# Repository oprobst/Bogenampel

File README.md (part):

# Bogenampel

Eine funkgesteuerte Timer-Anzeige für Bogenschießplätze — zwei Geräte, zwei Taster,
kein Pairing, kein Netzwerk.

---

**Inhalt** — [1. Das Projekt](#1-das-projekt) · [2. Entwicklung](#2-entwicklung)

---

# 1. Das Projekt

## Optimierungspotentiale

* Auch mit dem 12-V-Buzzer ist das Signal in einer großen Halle mit Hintergrundgeräuschen noch zu leise.
Für die nächste Version wird deshalb vorgeschlagen, alternativ eine Box per Bluetooth anzuschließen.

* Weiterhin ist das Gehäuse alles andere als wartungsfreundlich. Hier sollten vor allem die Bohrungen noch mal überdacht werden.

## Worum es geht

Auf dem Schießplatz gibt eine Ampel den Takt vor: Rot heißt warten, Grün heißt
schießen, die Restzeit läuft sichtbar herunter. Die Bogenampel macht genau das —
aber ohne Kabel zwischen Schießlinie und Zielbereich, und mit so wenig Bedienung
wie möglich.

An der Bedieneinheit wird einmal der Modus vorgewählt (120 oder 240 Sekunden,
1-2 oder 3-4 Schützen), danach steuern **zwei Taster** den kompletten
Turnierablauf. Die Einstellung überlebt das Ausschalten.

Die Anlage besteht aus zwei Geräten:

- **Bedieneinheit (Sender)** — liegt an der Schießlinie. Akkubetrieben, e-Paper-Display,
  zwei große Taster.
- **Anzeigeeinheit (Empfänger)** — steht am Ziel. Große dreistellige 7-Segment-Anzeige
  aus LED-Streifen, in Ampelfarben, dazu zwei Gruppenbalken.

Dazwischen läuft ESP-NOW auf Kanal 1 — kein WLAN, kein Accesspoint, kein Pairing.
Der Sender sucht den Empfänger beim Einschalten selbst und merkt sich dessen
MAC-Adresse zur Laufzeit.

**Das wichtigste Sicherheitsmerkmal ist ein Stück Nicht-Verhalten**: Der Empfänger
zählt eine gestartete Passe **autonom** zu Ende. Fällt der Funk aus oder geht der
Sender aus, läuft der Timer trotzdem korrekt ab und schaltet danach auf Rot. Die
Anzeige bleibt nie in Grün stehen, nur weil die Verbindung weg ist.

## Die Bedieneinheit

ESP32-S3-WROOM-1U mit externer Antenne am U.FL-Anschluss, 1,54″-e-Paper
(200 × 200, SSD1681), eine 14500-LiIon-Zelle mit MCP73837-Lader und ein
Soft-Power-Latch um einen TPS62742: Einschalten per Taster, Ausschalten übernimmt
die Firmware selbst, sobald sie fertig aufgeräumt hat.
Das e-Paper behält sein Bild ohne Strom — der Abschaltbildschirm bleibt deshalb nach
dem Ausschalten lesbar stehen.

Die Platine trägt den Namen „Universal ESP32 Fernbedienung V3" — sie ist bewusst
etwas allgemeiner gehalten als nötig. Links sitzen Ladeteil und USB-C, in der Mitte
das Funkmodul mit den beiden Tastern, rechts die Ansteuerung für das e-Paper.

## Die Anzeigeeinheit

Ein XIAO ESP32C3 treibt einen WS2811-Streifen mit **66 Pixeln**: 12 für den
Gruppenbalken C/D, 12 für A/B und 3 × 14 für die dreistellige Ziffernanzeige
(2 Pixel je Segment). Versorgt wird alles aus einem USB-C-Netzteil, das über einen
CH224K-Trigger auf **12 V** verhandelt wird.

Drei Potis regeln direkt am Gerät, ohne Umweg über den Funk: **Lautstärke**,
**Helligkeit** und **Lüfterdrehzahl**. Dazu ein Piezo-Transducer für die
Signaltöne und ein temperaturunkritischer, aber hörbarer Lüfter — deshalb regelbar.

## Bedienung

Der Sender hat zwei Taster. Welcher Taster einschaltet, legt der Power-Latch in der
Hardware fest — das ist die **CONFIG**-Taste.

| Taste | kurz | 3× schnell klicken | 3 s halten |
|---|---|---|---|
| **CONFIG** | Weiter / Wert ändern | — | Ausschalten |
| **OK** | Bestätigen / Passe beenden | Alarm | Ausschalten |

Einschalten: CONFIG drücken. Ausschalten: eine der beiden Tasten 3 Sekunden halten.
Die Konfiguration (Schießzeit, Schützenzahl) bleibt im NVS erhalten und steht beim
nächsten Einschalten wieder zur Verfügung.

**Alarm**: die **OK**-Taste dreimal schnell hintereinander drücken (höchstens 0,4 s
zwischen den Klicks). Das geht im Schießbetrieb und beim Pfeileholen — also überall
dort, wo Leute an der Schießlinie stehen können. Im Konfigurationsmenü und im
Startbildschirm bleibt die Folge bewusst wirkungslos. CONFIG löst grundsätzlich
keinen Alarm aus: Diese Taste blättert durch Menüs und zählt Werte hoch, dort ist
zügiges Tippen normale Bedienung. Quittiert wird ein Alarm mit einem kurzen OK.

Ausschalten und Alarm liegen absichtlich auf **verschiedenen** Bewegungen: Halten
schaltet immer aus, egal in welchem Zustand das Gerät gerade ist. Früher hing die
Bedeutung des Haltens am Betriebszustand — wer im Schießbetrieb ausschalten wollte,
löste stattdessen einen Alarm aus.

**Automatische Abschaltung**: Wird im Konfigurationsmenü oder in „Pfeile holen" 60 Minuten
lang keine Taste gedrückt, schaltet sich der Sender selbst ab und zeigt dabei
„Automatische Abschaltung". Im Schießbetrieb und bei stehendem Alarm greift das
bewusst **nicht** — dort läuft eine Passe bzw. ein Sicherheitszustand. Gedacht ist es
gegen das im Koffer vergessene Gerät; dagegen hilft keine Stromsparmaßnahme, nur
Ausschalten.

## Ablauf einer Passe

| Phase | Anzeige | Dauer |
|---|---|---|
| **Stopp** | Rot, `000` | bis zum Start |
| **Vorbereitung** | Rot, Countdown | 10 s |
| **Schießzeit** | Grün, Countdown | 120 s oder 240 s |
| **letzte 30 s** | Orange, Countdown | 30 s |
| **Ende** | Rot, `000` | — |

Der Piezo quittiert die Phasenwechsel mit kurzen Tonfolgen (3250 Hz), das Passenende
mit drei Tönen. Ein ausgelöster Alarm blinkt und piept achtmal.

### Gruppen und halbe Passe

Bei 3-4 Schützen wird zwischen den Gruppen A/B und C/D umgeschaltet; die Anzeige folgt
einem 4er-Zyklus. Zusätzlich lässt sich eine halbe Passe starten, wenn nur noch die
zweite Gruppe schießt. Den Wechsel von der ersten auf die zweite Hälfte vollzieht der
Empfänger selbst, sobald sein Countdown abgelaufen ist — auch das gehört zur
Autonomie-Regel oben.

## Schaltpläne und Platinen

Autoritativ sind die KiCad-Projekte [`Schaltung-Sender/`](Schaltung-Sender/) und
[`Schaltung-Empfaenger/`](Schaltung-Empfaenger/). Die folgenden Exporte sind für alle
gedacht, die ohne KiCad hineinsehen wollen.

**Bedieneinheit (Sender)**

**Anzeigeeinheit (Empfänger)**

---

## 3D-Druckteile
Der 3D-Druck ist noch bei weitem nicht optimal. Manche Bohrlöcher sind redundant, manche schlecht erreichbar.

Generell wurde mit schwarzem und weißem PETG gedruckt, für die Verschraubungen wurden Einschmelzgewinde genutzt. Damit der Aufbau verstärkt wird, ist oben und unten abgewinkeltes Stahlblech über die ganze Breite verschraubt.

# 2. Entwicklung

## Hardware-Überblick

| | Sender (Bedieneinheit) | Empfänger (Anzeigeeinheit) |
|---|---|---|
| **Controller** | ESP32-S3-WROOM-1U-N16R8 (16 MB Flash, 8 MB PSRAM) | Seeed XIAO ESP32C3 |
| **Anzeige** | 1.54″ e-Paper, 200×200 (SSD1681) | LED-Strip WS2811 12 V, 66 Pixel |
| **Funk** | ESP-NOW, Kanal 1 (im Chip integriert) | ESP-NOW, Kanal 1 |
| **Versorgung** | LiIon 14500 + MCP73837-Lader, USB-C | USB-C PD 12 V über CH224K (≥ 2 A) |
| **Bedienelemente** | 2 Taster (CONFIG, OK) | Debug-Taster, 3 Potis |
| **Sonstiges** | Soft-Power-Latch (TPS62742) | Piezo 12 V, geregelter Lüfter, Pegelwandler 74AHCT1G125 |
| **Firmware** | [`Sender/`](Sender/) | [`Empfaenger/`](Empfaenger/) |
| **Schaltplan** | [`Schaltung-Sender/`](Schaltung-Sender/) | [`Schaltung-Empfaenger/`](Schaltung-Empfaenger/) |

Die verbindliche Pin-Belegung steht in
[`specs/004-v3-esp32-port/contracts/hardware-pins.md`](specs/004-v3-esp32-port/contracts/hardware-pins.md)
und wird aus den KiCad-Netzlisten abgeleitet. Bei Abweichungen gilt der Schaltplan —
Änderungen gehören zuerst dorthin, dann in den Code.

Die Empfänger-Platine erzeugt aus den 12 V zwei weitere Schienen: ein TSR0.5-2433
versorgt den XIAO mit 3,3 V, ein L7805 den Pegelwandler mit 5 V. Der LED-Strip hängt
direkt am 12-V-Netz — er kann die Logikversorgung also nicht mehr in die Knie zwingen.

## Funk

ESP-NOW auf Kanal 1, ohne externes Funkmodul und ohne Pairing: Der Sender sucht den
Empfänger beim Start per Broadcast und merkt sich dessen MAC-Adresse zur Laufzeit.

Jeder Frame ist 6 Byte groß und trägt Magic-Bytes, eine Prüfsumme und eine
Sequenznummer; der Empfänger verwirft doppelte und fehlerhafte Pakete. Übertragen
werden 11 Kommandos (Start 120/240, Stopp, Init, Alarm, Ping, Gruppenwahl, halbe Passe).
Beim Start misst der Sender die Verbindungsqualität mit 10 Pings und zeigt das Ergebnis
im Splash-Screen.

> **Ein Radio, ein Kanal.** Der ESP32 kann nicht gleichzeitig ESP-NOW auf Kanal 1 und
> WLAN auf einem anderen Kanal betreiben. Deshalb läuft im Normalbetrieb **kein** WiFi —
> weder ein Accesspoint noch eine Netzwerkverbindung. Für Updates gibt es den
> Wartungsmodus (siehe unten).

Die Protokollregeln stehen in
[`espnow-protocol.md`](specs/004-v3-esp32-port/contracts/espnow-protocol.md). Zwei
davon sind beim Ändern leicht zu übersehen:

- **Regel 3**: Ein `CMD_START` wird vom Empfänger ignoriert, solange seine
  Vorbereitungsphase bereits läuft. Beim regulären Gruppenwechsel ist das Kommando
  nur ein Sync-Signal — der Empfänger hat da längst selbst umgeschaltet.
- **FR-004a**: Beim Ablauf der Zeit sendet der Sender **nie** `CMD_STOP`. Das
  Passenende gehört dem Empfänger allein.

## Bauen und Flashen

PlatformIO ist der einzige unterstützte Build-Pfad. Die `platformio.ini` liegt **zentral
im Repo-Root**, nicht in den Firmware-Ordnern — das Repo-Root ist das Arbeitsverzeichnis.
Bibliotheken kommen über `lib_deps`, es muss nichts manuell installiert werden; die
Versionen sind **gepinnt** (FastLED 3.10.3, GxEPD2 1.6.9, Adafruit GFX 1.12.6).

```bash
pio run -e sender                 # bauen
pio run -e empfaenger

pio run -t upload -e sender       # per USB flashen
pio device monitor -e sender      # 115200 Baud

pio run -e sender-release         # Feld-Build: ohne Debug-Ausgaben und CDC-Task
```

Drei Stolpersteine, die alle wie Hardwaredefekte aussehen:

**Beim Sender muss CONFIG während des gesamten Uploads gedrückt bleiben.** Der Reset von
esptool lässt sonst den Power-Latch fallen; das Gerät schaltet sich mitten im Flashen ab
und der USB-Port verschwindet. Zu beachten: `pio run -t upload` startet esptool erst nach
gut einer Minute Build- und Dependency-Scan — so lange muss der Taster gehalten werden.
Praktischer ist, das Gerät **mit gehaltenem CONFIG einzuschalten** (dann greift der
Boot-Lockout und das Halten löst keine Power-Off-Geste aus) und esptool direkt mit den
vier Images aufzurufen.

**Die Upload-Baudrate darf nicht hochgesetzt werden** (`upload_speed = 115200` in der
`platformio.ini`). Der Sender flasht über die native USB-Serial/JTAG-Peripherie, wo die
Baudrate bedeutungslos ist — esptool wechselt beim Board-Default 460800 trotzdem, der Port
re-enumeriert dabei und der Upload stirbt mitten im Stub-Flasher mit
`PermissionError(13) ... Cannot configure port`.

**Unter Windows vor jedem Upload `$env:PYTHONIOENCODING="utf-8"` setzen.** Sonst bricht
der Vorgang mit `UnicodeEncodeError` und `[upload] Error 4294967295` ab — esptool schreibt
Unicode-Fortschrittsbalken, die eine cp1252-Konsole nicht kodieren kann. Auf den Chip
wurde zu diesem Zeitpunkt noch nichts geschrieben.

### Testlauf mit verkürzten Zeiten

Für Tests gibt es eigene Environments: Vorbereitung 5 s statt 10, Schießzeit 6 s statt
120 bzw. 12 s statt 240, Orange-Phase 2 s statt 30. Eine komplette Passe läuft damit in
unter einer Minute durch.

```bash
pio run -t upload -e empfaenger-debug-ota
pio run -t upload -e sender-debug-ota
```

Eingeschaltet wird das über `-DDEBUG_SHORT_TIMES=1` aus der `platformio.ini` — **nicht**
im Quellcode, wo ein `#ifndef`-Guard mit Default 0 steht. So kann ein Build mit
6-Sekunden-Passe nicht versehentlich im Feld landen.

> **Immer beide Geräte umstellen.** Der Empfänger zählt die Passe autonom und bekommt
> per Funk nur `CMD_START_120/240`, nie die Dauer selbst. Die Zeittabelle
> (`Timing::shootingSeconds()`) steht wortgleich in beiden `Config.h` und muss es
> bleiben — sonst endet die Passe auf zwei verschiedenen Sekunden.

### OTA-Wartungsmodus

Beide Geräte lassen sich drahtlos aktualisieren, aber nur in einem eigenen Betriebsmodus —
im Normalbetrieb ist WiFi aus (siehe Kasten oben).

- **Sender**: beide Taster gleichzeitig gedrückt halten und einschalten
- **Empfänger**: mit gehaltenem Debug-Taster (D7) einschalten

Der Sender zeigt daraufhin einen Wartungs-Screen mit WLAN-Status und **seiner eigenen
IP-Adresse**; beim Empfänger signalisiert die Status-LED durch langsames Blinken, dass er
bereit ist. Die IP wird als `upload_port` in der `platformio.ini` eingetragen (eine feste
DHCP-Reservierung ist empfehlenswert, mDNS-Namen lösen über Subnetzgrenzen nicht
zuverlässig auf).

```bash
pio run -t upload -e sender-ota            # Sender, Debug-Build (serieller Monitor bleibt)
pio run -t upload -e sender-release-ota    # Sender, Feld-Build (ohne Debug-Ausgaben/CDC)
pio run -t upload -e empfaenger-ota
```

`sender-release-ota` ist der Auslieferungsweg: gleicher Wartungsmodus, aber das
Image aus `sender-release`. Danach meldet sich kein serieller Port mehr — der
Rückweg auf den Debug-Build geht weiterhin per OTA über `sender-ota`, solange der
Wartungsmodus erreichbar bleibt.

Voraussetzung ist eine `wifi_credentials.h` im Repo-Root — Vorlage:
[`wifi_credentials.h.example`](wifi_credentials.h.example). Die Datei ist bewusst nicht
eingecheckt. Fehlt sie, meldet der Wartungsmodus das auf dem Display und wartet; einen
Accesspoint-Fallback gibt es absichtlich nicht, weil ein zweites Netz auf fremdem Kanal
ESP-NOW stilllegen würde.

Zur Fehlersuche: **ArduinoOTA lauscht auf UDP 3232, nicht TCP.** Ein TCP-Portscan meldet den
Port folgerichtig als geschlossen, auch wenn der Wartungsmodus einwandfrei läuft — daraus
lässt sich also nichts über die Erreichbarkeit ableiten. espota schickt eine UDP-Einladung,
woraufhin das Gerät eine TCP-Rückverbindung zum Host aufbaut.

Der Zugang ist nicht durch ein Passwort geschützt, sondern dadurch, dass der Modus nur mit
physisch gedrückten Tastern erreichbar ist. Grund: Das ArduinoOTA-Passwort (PBKDF2) ist mit
der `espota.py` von PlatformIO nicht kompatibel, die Authentifizierung scheitert stumm.

## Anzeige-Eigenheiten

Zwei Stellen, an denen das naheliegende Verhalten bewusst nicht implementiert ist:

**Das e-Paper blitzt nur beim Start und beim Beenden.** Ein Voll-Refresh (~2,6 s,
schwarz/weiß-Invertierung) läuft nur im Splash und auf dem Abschaltbildschirm. Alles
dazwischen — Menü, Countdown, Pfeile holen, Alarm — nutzt die Partial-Waveform und
bleibt ruhig. Restschatten werden dafür in Kauf genommen und erst beim nächsten
Einschalten weggeblitzt. Die Entwicklungsgeschichte dieser Stelle steht als Kommentar
in `Sender/EpaperDisplay.cpp`; sie ist zweimal in die andere Richtung gelaufen.

**Die Poti-Drehrichtung sitzt an genau einer Stelle**: `Poti::ASCENDING` und
`Poti::level()` in `Empfaenger/Config.h`. Alle Kennlinien rechnen mit der
Reglerstellung, nie mit dem ADC-Rohwert. Wer eine Drehrichtung umdreht, ändert das
Flag — nicht die einzelnen Kennlinien.

## Stromverbrauch des Senders

Gemessen am laufenden Gerät: **0,39 W → 0,20 W**, also etwa doppelte Akkulaufzeit.
Zwei Maßnahmen, beide in der Firmware:

| Maßnahme | Ersparnis |
|---|---|
| CPU-Takt 240 → 80 MHz (`System::CPU_FREQ_NORMAL_MHZ`) | ~10 mA |
| ESP-NOW-Empfangsfenster duty-cycled statt dauerhaft offen | ~38 mA |

Der Löwenanteil war das Funkmodul: ESP-NOW hält den Empfänger per Default dauerhaft an.
Der Sender ist nach der Discovery aber ein reiner Sender — das ACK auf eigene Frames
kommt im Sendefenster zurück, also darf das Empfangsfenster zu bleiben. Während der
Discovery wird es nur um den HELLO-Broadcast herum geöffnet. Details und Voraussetzungen
stehen in [`espnow-protocol.md`](specs/004-v3-esp32-port/contracts/espnow-protocol.md),
Regel 7.

Das **e-Paper ist für den Verbrauch praktisch irrelevant** (unter 2 %) — der
Sekundencountdown im Schießbetrieb ist bewusst nicht angetastet. Nicht möglich ist das
Abschalten des PSRAM: `CONFIG_SPIRAM=1` steckt in allen vorkompilierten
arduino-esp32-Varianten und die Initialisierung hängt nicht an `-DBOARD_HAS_PSRAM`.
Weiter runter käme man nur mit abgeschaltetem Radio zwischen den Kommandos und
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
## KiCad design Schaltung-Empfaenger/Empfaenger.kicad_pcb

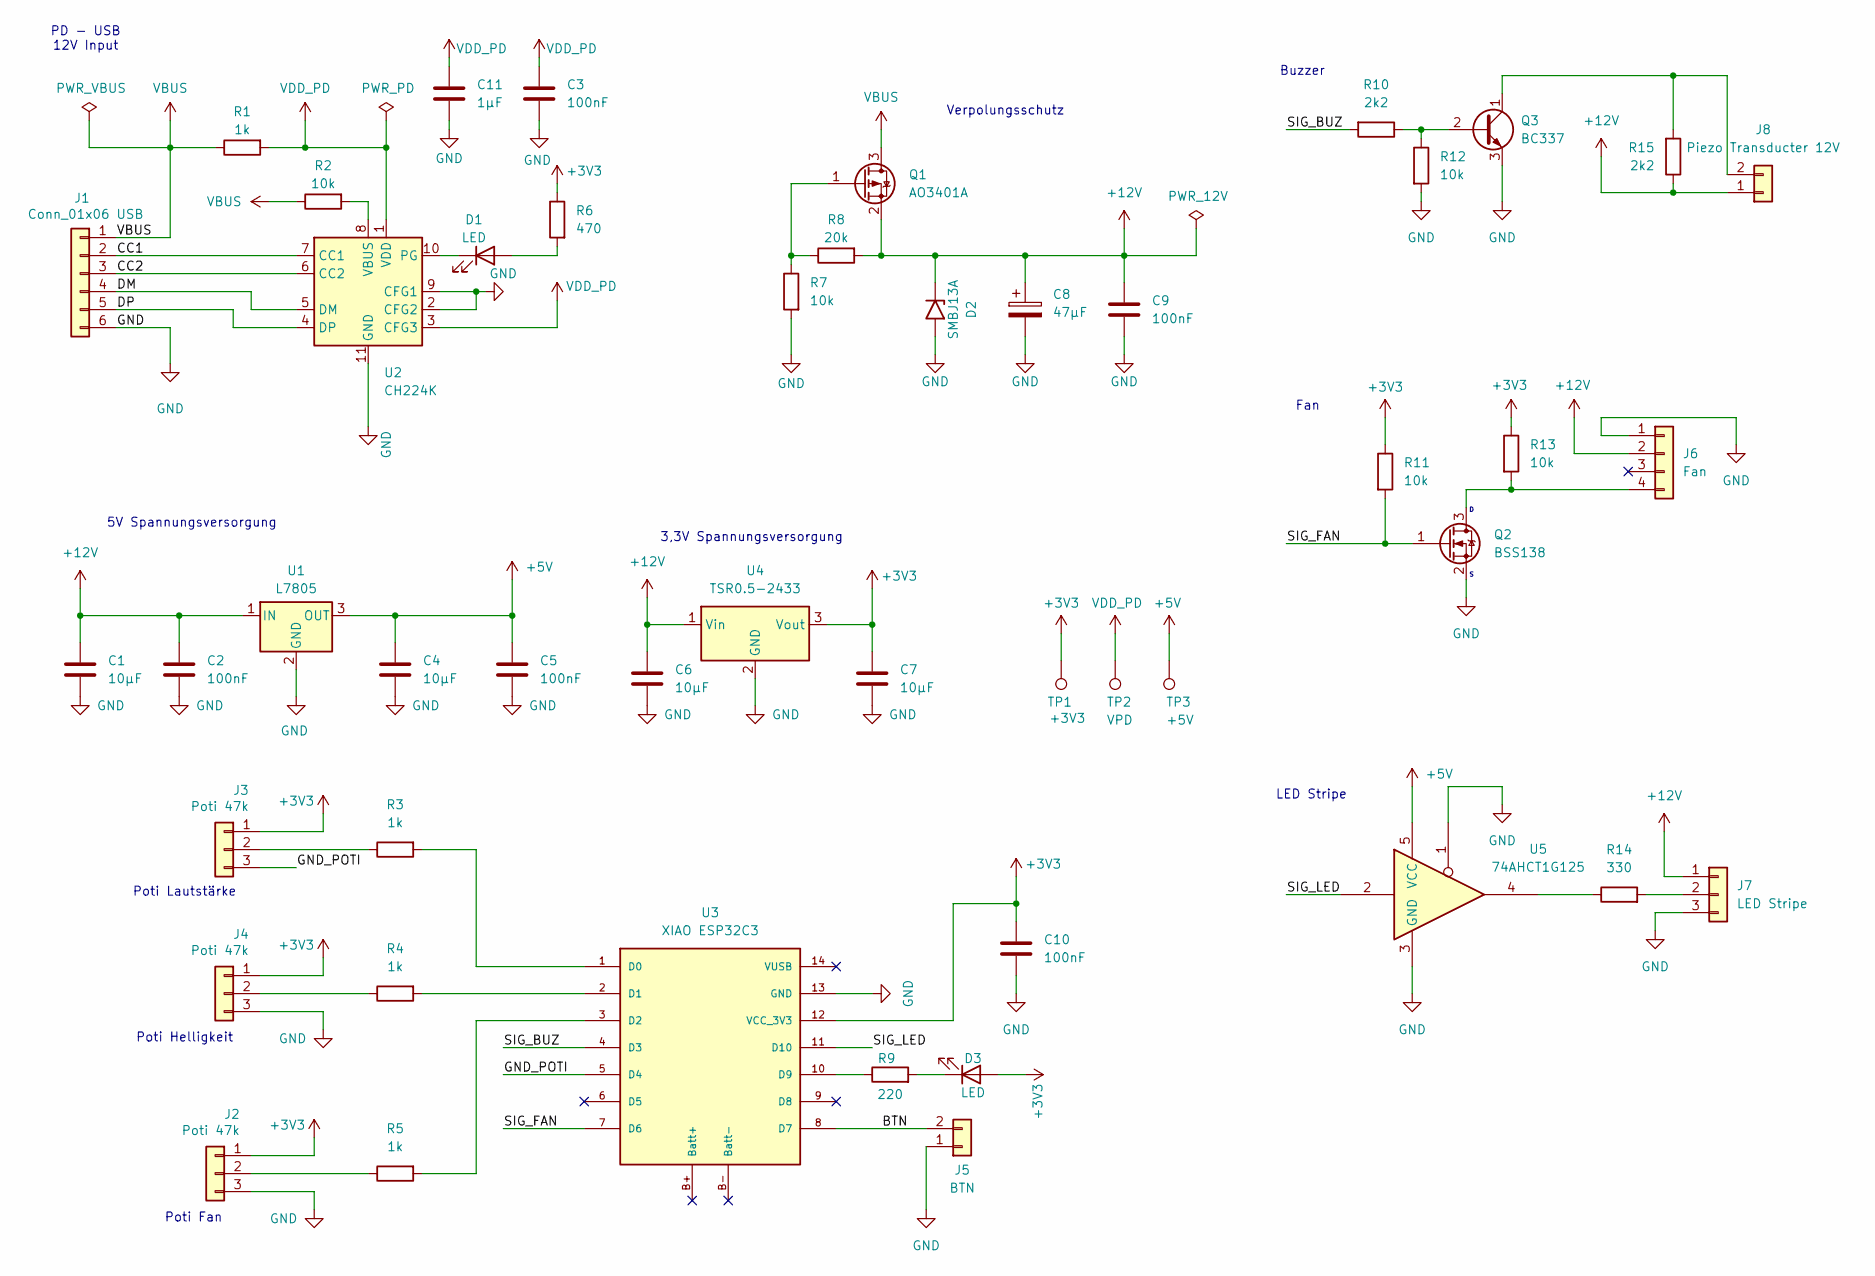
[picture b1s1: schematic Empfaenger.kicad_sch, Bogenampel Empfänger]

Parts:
C1, C4, C6, C7: 10µF; C_1206_3216Metric
C2, C3, C5, C9, C10: 100nF; C_1206_3216Metric
C8: 47µF; CP_Radial_D8.0mm_P3.50mm
C11: 1µF; C_1206_3216Metric
D1, D3: LED; LED_D5.0mm
D2: SMBJ13A; D_SMB
J1: Conn_01x06 USB; JST_XH_B6B-XH-AM_1x06_P2.50mm_Vertical
J2, J3, J4: Poti 47k; JST_XH_B3B-XH-AM_1x03_P2.50mm_Vertical
J5: BTN; JST_XH_B2B-XH-AM_1x02_P2.50mm_Vertical
J6: Fan; JST_XH_B4B-XH-AM_1x04_P2.50mm_Vertical
J7: LED Stripe; JST_XH_B3B-XH-AM_1x03_P2.50mm_Vertical
J8: Piezo Transducter 12V; JST_XH_B2B-XH-AM_1x02_P2.50mm_Vertical
Q1: AO3401A; SOT-23
Q2: BSS138; SOT-23; MPN 2N7002
Q3: BC337; TO-92_Inline
R1: 1k; R_1206_3216Metric
R2, R7, R11, R12, R13: 10k; R_0603_1608Metric
R3, R4, R5: 1k; R_0603_1608Metric
R6: 470; R_0603_1608Metric
R8: 20k; R_0603_1608Metric
R9: 220; R_0603_1608Metric
R10, R15: 2k2; R_0603_1608Metric
R14: 330; R_0603_1608Metric
TP1: +3V3; TestPoint_Pad_D1.5mm
TP2: VPD; TestPoint_Pad_D1.5mm
TP3: +5V; TestPoint_Pad_D1.5mm
U1: L7805; TO-220-3_Vertical
U2: CH224K; SSOP-10-1EP_3.9x4.9mm_P1mm_EP2.1x3.3mm
U3: XIAO ESP32C3; xiao_esp32c3
U4: TSR0.5-2433; Converter_DCDC_TRACO_TSR0.5-24xx_TSR0.5-24xxx_THT
U5: 74AHCT1G125; SOT-353_SC-70-5

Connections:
+3V3: C7.1, C10.1, D3.2 (A), J2.1, J3.1, J4.1, R6.1, R11.1, R13.1, TP1.1 (1_1), U3.12 (VCC_3V3), U4.3 (Vout)
+5V: C4.1, C5.1, TP3.1 (1_1), U1.3 (OUT), U5.5 (VCC)
+12V: C1.1, C2.1, C6.1, C8.1, C9.1, D2.1 (A1), J6.2, J7.1, J8.1, Q1.2 (S), R8.2, R15.1, U1.1 (IN), U4.1 (Vin)
/BTN: J5.2, U3.8 (D7)
/CC1: J1.2, U2.7 (CC1)
/CC2: J1.3, U2.6 (CC2)
/DM: J1.4, U2.5 (DM)
/DP: J1.5, U2.4 (DP)
/GND_POTI: J3.3, U3.5 (D4)
/SIG_BUZ: R10.2, U3.4 (D3)
/SIG_FAN: Q2.1 (G), R11.2, U3.7 (D6)
/SIG_LED: U3.11 (D10), U5.2
GND: C1.2, C2.2, C3.2, C4.2, C5.2, C6.2, C7.2, C8.2, C9.2, C10.2, C11.2, D2.2 (A2), J1.6, J2.3, J4.3, J5.1, J6.1, J7.3, Q2.2 (S), Q3.3 (E), R7.2, R12.2, U1.2 (GND), U2.2 (CFG2), U2.9 (CFG1), U2.11 (GND), U3.13 (GND), U4.2 (GND), U5.1, U5.3 (GND)
unnamed: D1.2 (A), R6.2
unnamed: D1.1 (K), U2.10 (PG)
unnamed: D3.1 (K), R9.2
unnamed: J2.2, R5.1
unnamed: J3.2, R3.1
unnamed: J4.2, R4.1
unnamed: J6.4, Q2.3 (D), R13.2
unnamed: J7.2, R14.2
unnamed: J8.2, Q3.1 (C), R15.2
unnamed: Q1.1 (G), R7.1, R8.1
unnamed: Q3.2 (B), R10.1, R12.1
unnamed: R14.1, U5.4
unnamed: R2.2, U2.8 (VBUS)
unnamed: R3.2, U3.1 (D0)
unnamed: R4.2, U3.2 (D1)
unnamed: R5.2, U3.3 (D2)
unnamed: R9.1, U3.10 (D9)
VBUS: J1.1, Q1.3 (D), R1.1, R2.1
VDD_PD: C3.1, C11.1, R1.2, TP2.1 (1_1), U2.1 (VDD), U2.3 (CFG3)

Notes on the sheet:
Poti Lautstärke
Buzzer
Poti Helligkeit
LED Stripe
Fan
Verpolungsschutz
Poti Fan
3,3V Spannungsversorgung
5V Spannungsversorgung
PD - USB 12V Input

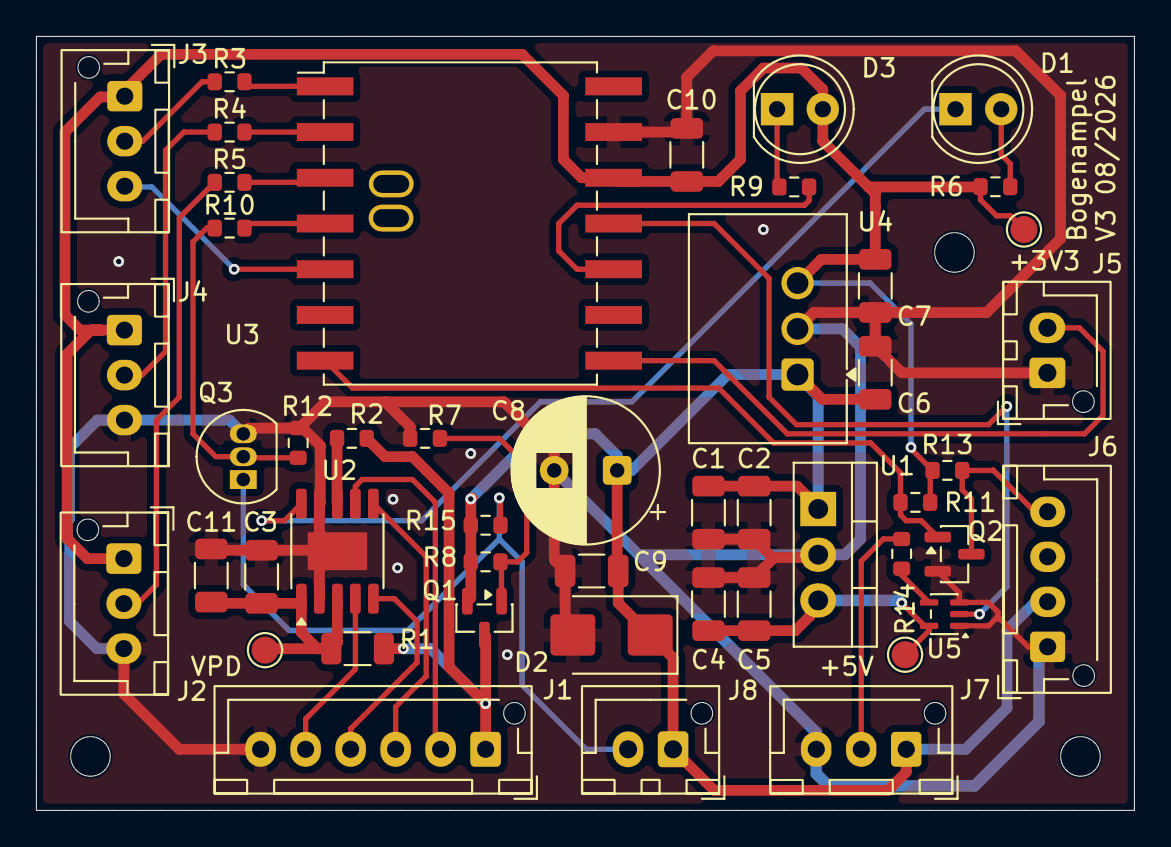
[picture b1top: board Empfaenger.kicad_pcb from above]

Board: 2 copper layers, 61.0 x 43.0 mm, 48 parts (0 on the bottom side), 32 nets.

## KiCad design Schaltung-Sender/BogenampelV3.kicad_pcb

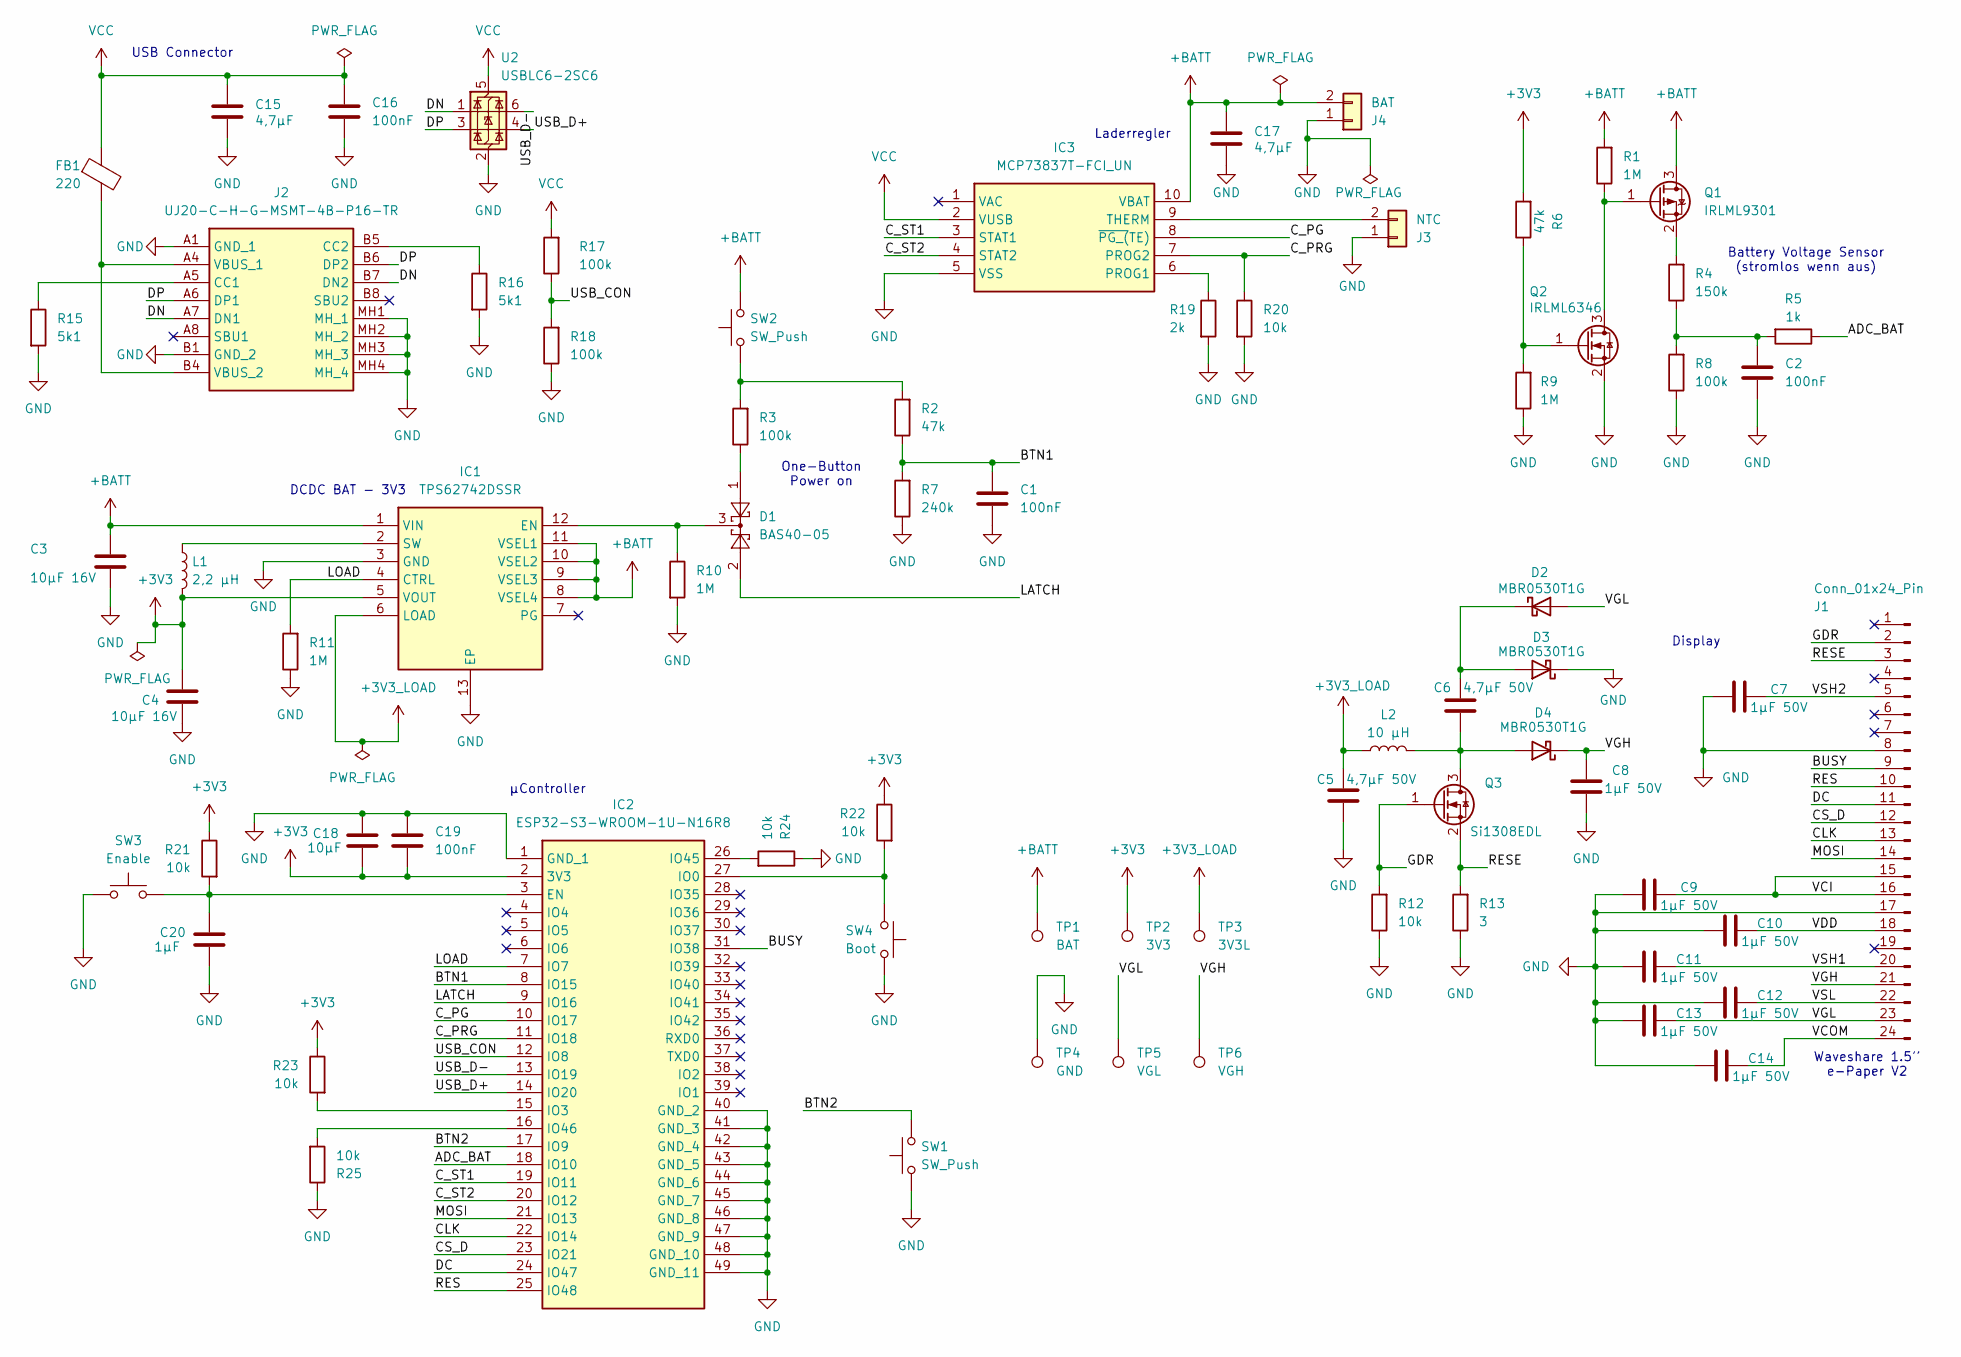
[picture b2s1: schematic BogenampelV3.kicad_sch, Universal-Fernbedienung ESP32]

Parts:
C1, C16, C19: 100nF; C_0603_1608Metric
C2: 100nF; C_0805_2012Metric
C3, C4: 10µF 16V; C_0805_2012Metric
C5, C6: 4,7µF 50V; C_1206_3216Metric
C7, C8, C9, C10, C11, C12, C13, C14: 1µF 50V; C_0805_2012Metric
C15, C17: 4,7µF; C_0805_2012Metric
C18: 10µF; C_0805_2012Metric
C20: 1µF; C_0805_2012Metric
D1: BAS40-05; SOT-23
D2, D3, D4: MBR0530T1G; D_SOD-123
FB1: 220; R_0805_2012Metric
IC1: TPS62742DSSR; SON50P200X300X80-13N-D; Mouser Part Number 595-TPS62742DSSR
IC2: ESP32-S3-WROOM-1U-N16R8; ESP32S3WROOM1UN16R8; Mouser Part Number 356-ESP32S3WM1UN16R8
IC3: MCP73837T-FCI_UN; SOP50P490X110-10N; Mouser Part Number 579-MCP73837T-FCI/UN
J1: Conn_01x24_Pin; Hirose_FH12-24S-0.5SH_1x24-1MP_P0.50mm_Horizontal
J2: UJ20-C-H-G-MSMT-4B-P16-TR; UJ20CHGMSMT4BP16TR; Manufacturer_Part_Number UJ20-C-H-G-MSMT-4B-P16-TR
J3: NTC; PinHeader_1x02_P2.54mm_Vertical; MPN 61300211121
J4: BAT; PinHeader_1x02_P2.54mm_Vertical; MPN 61300211121
L1: 2,2 µH; L_Coilcraft_LPS3314
L2: 10 µH; L_Coilcraft_LPS3314
Q1: IRLML9301; SOT-23
Q2: IRLML6346; SOT-23
Q3: Si1308EDL; SOT-323_SC-70
R1, R9, R10, R11: 1M; R_1206_3216Metric
R2, R6: 47k; R_1206_3216Metric
R3, R8, R17, R18: 100k; R_1206_3216Metric
R4: 150k; R_1206_3216Metric
R5: 1k; R_1206_3216Metric
R7: 240k; R_1206_3216Metric
R12, R20, R21, R22, R23, R24, R25: 10k; R_1206_3216Metric
R13: 3; R_1206_3216Metric
R15, R16: 5k1; R_1206_3216Metric
R19: 2k; R_1206_3216Metric
SW1, SW2: SW_Push; SW_PUSH-12mm_Wuerth-430476085716
SW3: Enable; SW_PUSH_6mm_H5mm
SW4: Boot; SW_PUSH_6mm_H5mm
TP1: BAT; TestPoint_Pad_D1.5mm
TP2: 3V3; TestPoint_Pad_D1.5mm
TP3: 3V3L; TestPoint_Pad_D1.5mm
TP4: GND; TestPoint_Pad_1.5x1.5mm
TP5: VGL; TestPoint_Pad_D1.5mm
TP6: VGH; TestPoint_Pad_D1.5mm
U2: USBLC6-2SC6; SOT-23-6

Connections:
+3V3: C4.1, C18.2, C19.2, IC1.5 (VOUT), IC2.2 (3V3), L1.2, R6.2, R21.1, R22.1, R23.1, TP2.1 (1_1)
+3V3_LOAD: C5.1, IC1.6 (LOAD), L2.1, TP3.1 (1_1)
+BATT: C3.1, C17.1, IC1.1 (VIN), IC1.8 (VSEL4), IC1.9 (VSEL3), IC1.10 (VSEL2), IC1.11 (VSEL1), IC3.10 (VBAT), J4.2, Q1.3 (D), R1.2, SW2.2, TP1.1 (1_1)
/ADC_BAT: IC2.18 (IO10), R5.1
/BTN1: C1.1, IC2.8 (IO15), R2.1, R7.2
/BTN2: IC2.17 (IO9), SW1.2
/BUSY: IC2.31 (IO38), J1.9
/CLK: IC2.22 (IO14), J1.13
/CS_D: IC2.23 (IO21), J1.12
/C_PG: IC2.10 (IO17), IC3.8 (~PG_(TE))
/C_PRG: IC2.11 (IO18), IC3.7 (PROG2), R20.1
/C_ST1: IC2.19 (IO11), IC3.3 (STAT1)
/C_ST2: IC2.20 (IO12), IC3.4 (STAT2)
/DC: IC2.24 (IO47), J1.11
/DN: J2.A7 (DN1), J2.B7 (DN2), U2.1 (I/O1)
/DP: J2.A6 (DP1), J2.B6 (DP2), U2.3 (I/O2)
/GDR: J1.2, Q3.1 (G), R12.2
/LATCH: D1.2, IC2.9 (IO16)
/LOAD: IC1.4 (CTRL), IC2.7 (IO7), R11.2
/MOSI: IC2.21 (IO13), J1.14
/RES: IC2.25 (IO48), J1.10
/RESE: J1.3, Q3.2 (S), R13.2
/USB_CON: IC2.12 (IO8), R17.1, R18.2
/USB_D+: IC2.14 (IO20), U2.4 (I/O2)
/USB_D-: IC2.13 (IO19), U2.6 (I/O1)
/VCI: C9.2, J1.15, J1.16
/VCOM: C14.2, J1.24
/VDD: C10.2, J1.18
/VGH: C8.2, D4.1 (K), J1.21, TP6.1 (1_1)
/VGL: C13.2, D2.2 (A), J1.23, TP5.1 (1_1)
/VSH1: C11.2, J1.20
/VSH2: C7.2, J1.5
/VSL: C12.2, J1.22
GND: C1.2, C2.2, C3.2, C4.2, C5.2, C7.1, C8.1, C9.1, C10.1, C11.1, C12.1, C13.1, C14.1, C15.2, C16.2, C17.2, C18.1, C19.1, C20.2, D3.1 (K), IC1.3 (GND), IC1.13 (EP), IC2.1 (GND_1), IC2.40 (GND_2), IC2.41 (GND_3), IC2.42 (GND_4), IC2.43 (GND_5), IC2.44 (GND_6), IC2.45 (GND_7), IC2.46 (GND_8), IC2.47 (GND_9), IC2.48 (GND_10), IC2.49 (GND_11), IC3.5 (VSS), J1.8, J1.17, J2.A1 (GND_1), J2.B1 (GND_2), J2.MH1 (MH_1), J2.MH2 (MH_2), J2.MH3 (MH_3), J2.MH4 (MH_4), J3.1, J4.1, Q2.2 (S), R7.1, R8.1, R9.1, R10.2, R11.1, R12.1, R13.1, R15.2, R16.2, R18.1, R19.2, R20.2, R24.1, R25.1, SW1.1, SW3.1, SW4.1, TP4.1 (1_1), U2.2 (GND)
unnamed: C2.1, R4.1, R5.2, R8.2
unnamed: D1.1, R3.1
unnamed: C6.2, D2.1 (K), D3.2 (A)
unnamed: C6.1, D4.2 (A), L2.2, Q3.3 (D)
unnamed: D1.3, IC1.12 (EN), R10.1
unnamed: IC1.2 (SW), L1.1
unnamed: C20.1, IC2.3 (EN), R21.2, SW3.2
unnamed: IC2.27 (IO0), R22.2, SW4.2
unnamed: IC2.15 (IO3), R23.2
unnamed: IC2.26 (IO45), R24.2
unnamed: IC2.16 (IO46), R25.2
unnamed: IC3.6 (PROG1), R19.1
unnamed: IC3.9 (THERM), J3.2
unnamed: J2.A5 (CC1), R15.1
unnamed: J2.B5 (CC2), R16.1
unnamed: FB1.2, J2.A4 (VBUS_1), J2.B4 (VBUS_2)
unnamed: Q1.1 (G), Q2.3 (D), R1.1
unnamed: Q1.2 (S), R4.2
unnamed: Q2.1 (G), R6.1, R9.2
unnamed: R2.2, R3.2, SW2.1
VCC: C15.1, C16.1, FB1.1, IC3.2 (VUSB), R17.2, U2.5 (VBUS)

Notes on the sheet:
USB Connector
Battery Voltage Sensor (stromlos wenn aus)
One-Button Power on
µController
Laderregler
Display
DCDC BAT - 3V3
Waveshare 1.5'' e-Paper V2

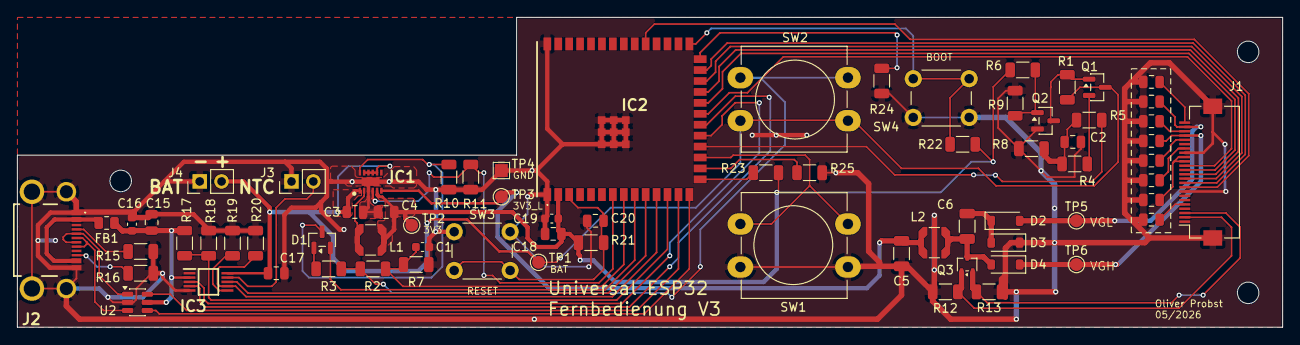
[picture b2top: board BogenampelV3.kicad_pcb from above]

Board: 2 copper layers, 147.0 x 36.0 mm, 72 parts (0 on the bottom side), 55 nets.

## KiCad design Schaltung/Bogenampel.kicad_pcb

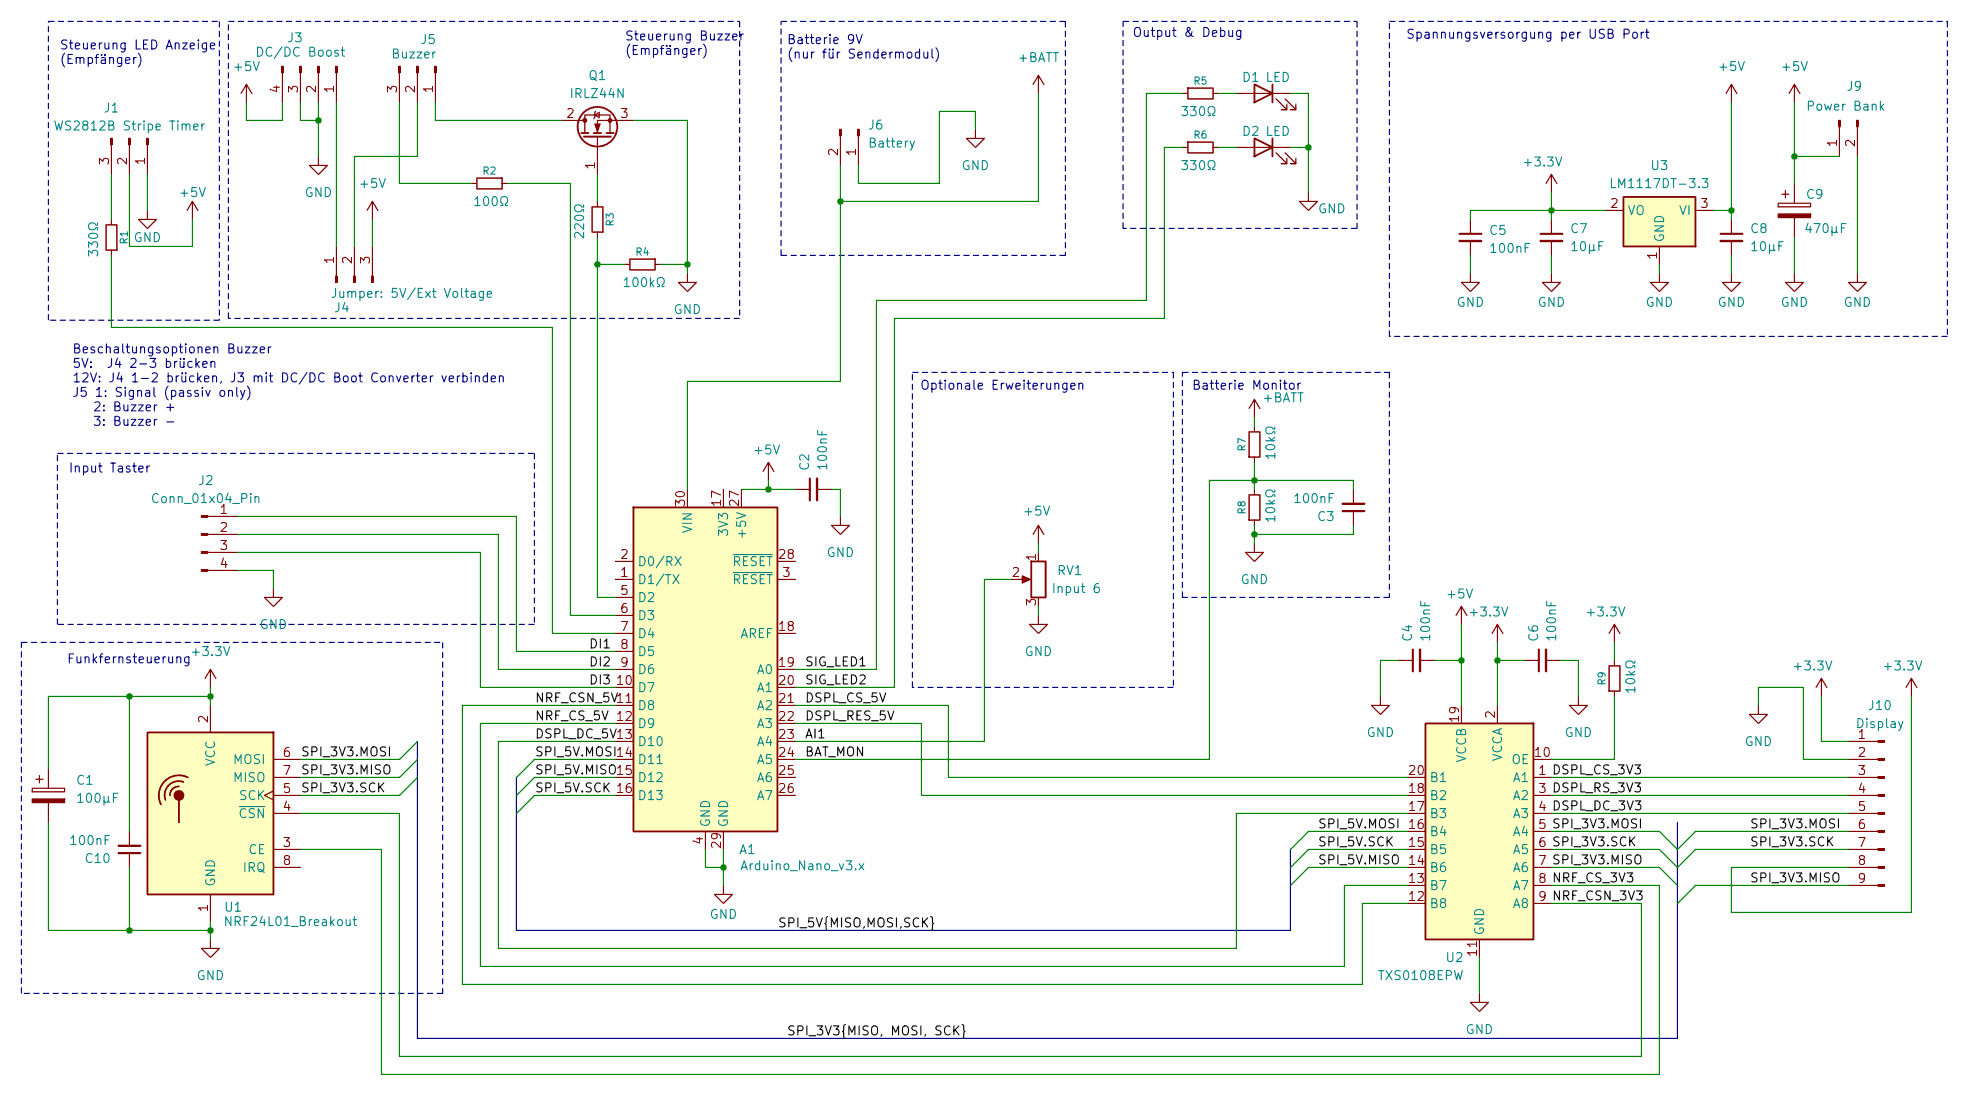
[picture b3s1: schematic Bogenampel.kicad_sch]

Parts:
A1: Arduino_Nano_v3.x; Arduino_Nano
C1: 100µF; CP_Radial_D8.0mm_P3.50mm
C2, C3, C4, C5, C6, C10: 100nF; C_1206_3216Metric
C7, C8: 10µF; C_1206_3216Metric
C9: 470µF; CP_Radial_D8.0mm_P3.50mm
D1, D2: LED; LED_D3.0mm
J1: WS2812B Stripe Timer; PhoenixContact_MCV_1,5_3-G-5.08_1x03_P5.08mm_Vertical
J2: Conn_01x04_Pin; JST_XH_B4B-XH-A_1x04_P2.50mm_Vertical
J3: DC/DC Boost; JST_XH_B4B-XH-A_1x04_P2.50mm_Vertical
J4: Jumper: 5V/Ext Voltage; PinHeader_1x03_P2.54mm_Vertical
J5: Buzzer; JST_XH_B3B-XH-A_1x03_P2.50mm_Vertical
J6: Battery; JST_XH_B2B-XH-A_1x02_P2.50mm_Vertical
J9: Power Bank; PhoenixContact_MCV_1,5_2-G-5.08_1x02_P5.08mm_Vertical
J10: Display; JST_EH_B9B-EH-A_1x09_P2.50mm_Vertical
Q1: IRLZ44N; TO-220-3_Vertical
R1, R5, R6: 330Ω; R_1206_3216Metric
R2: 100Ω; R_1206_3216Metric
R3: 220Ω; R_1206_3216Metric
R4: 100kΩ; R_1206_3216Metric
R7, R8, R9: 10kΩ; R_1206_3216Metric
RV1: Input 6; JST_XH_B3B-XH-A_1x03_P2.50mm_Vertical
U1: NRF24L01_Breakout; nRF24L01_Breakout
U2: TXS0108EPW; TSSOP-20_4.4x6.5mm_P0.65mm
U3: LM1117DT-3.3; TO-252-3_TabPin2

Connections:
+3.3V: C1.1, C5.1, C6.1, C7.1, C10.2, J10.1, J10.8, R9.2, U1.2 (VCC), U2.2 (VCCA), U3.2 (VO)
+5V: A1.27 (+5V), C2.1, C4.2, C8.1, C9.1, J1.2, J3.4, J4.3, J9.1, RV1.1, U2.19 (VCCB), U3.3 (VI)
+BATT: A1.30 (VIN), J6.2, R7.2
/AI1: A1.23 (A4), RV1.2
/BAT_MON: A1.24 (A5), C3.2, R7.1, R8.2
/DI1: A1.8 (D5), J2.1
/DI2: A1.9 (D6), J2.2
/DI3: A1.10 (D7), J2.3
/DSPL_CS_3V3: J10.3, U2.1 (A1)
/DSPL_CS_5V: A1.21 (A2), U2.20 (B1)
/DSPL_DC_3V3: J10.5, U2.4 (A3)
/DSPL_DC_5V: A1.13 (D10), U2.17 (B3)
/DSPL_RES_5V: A1.22 (A3), U2.18 (B2)
/DSPL_RS_3V3: J10.4, U2.3 (A2)
/NRF_CSN_3V3: U1.4 (~CSN), U2.9 (A8)
/NRF_CSN_5V: A1.11 (D8), U2.12 (B8)
/NRF_CS_3V3: U1.3 (CE), U2.8 (A7)
/NRF_CS_5V: A1.12 (D9), U2.13 (B7)
/SIG_LED1: A1.19 (A0), R5.1
/SIG_LED2: A1.20 (A1), R6.1
/SPI_3V3.MISO: J10.9, U1.7 (MISO), U2.7 (A6)
/SPI_3V3.MOSI: J10.6, U1.6 (MOSI), U2.5 (A4)
/SPI_3V3.SCK: J10.7, U1.5 (SCK), U2.6 (A5)
/SPI_5V.MISO: A1.15 (D12), U2.14 (B6)
/SPI_5V.MOSI: A1.14 (D11), U2.16 (B4)
/SPI_5V.SCK: A1.16 (D13), U2.15 (B5)
GND: A1.4 (GND), A1.29 (GND), C1.2, C2.2, C3.1, C4.1, C5.2, C6.2, C7.2, C8.2, C9.2, C10.1, D1.1 (K), D2.1 (K), J1.1, J2.4, J3.2, J3.3, J6.1, J9.2, J10.2, Q1.3 (S), R4.1, R8.1, RV1.3, U1.1 (GND), U2.11 (GND), U3.1 (GND)
unnamed: A1.5 (D2), R3.1, R4.2
unnamed: A1.6 (D3), R2.1
unnamed: A1.7 (D4), R1.1
unnamed: D1.2 (A), R5.2
unnamed: D2.2 (A), R6.2
unnamed: J1.3, R1.2
unnamed: J3.1, J4.1
unnamed: J4.2, J5.2
unnamed: J5.1, Q1.2 (D)
unnamed: J5.3, R2.2
unnamed: Q1.1 (G), R3.2
unnamed: R9.1, U2.10 (OE)

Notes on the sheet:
Steuerung Buzzer (Empfänger)
Beschaltungsoptionen Buzzer 5V: J4 2-3 brücken 12V: J4 1-2 brücken, J3 mit DC/DC Boot Converter verbinden J5 1: Signal (passiv only) 2: Buzzer + 3: Buzzer -
Input Taster
Steuerung LED Anzeige (Empfänger)
Spannungsversorgung per USB Port
Batterie 9V (nur für Sendermodul)
Batterie Monitor
Optionale Erweiterungen
Funkfernsteuerung
Output & Debug

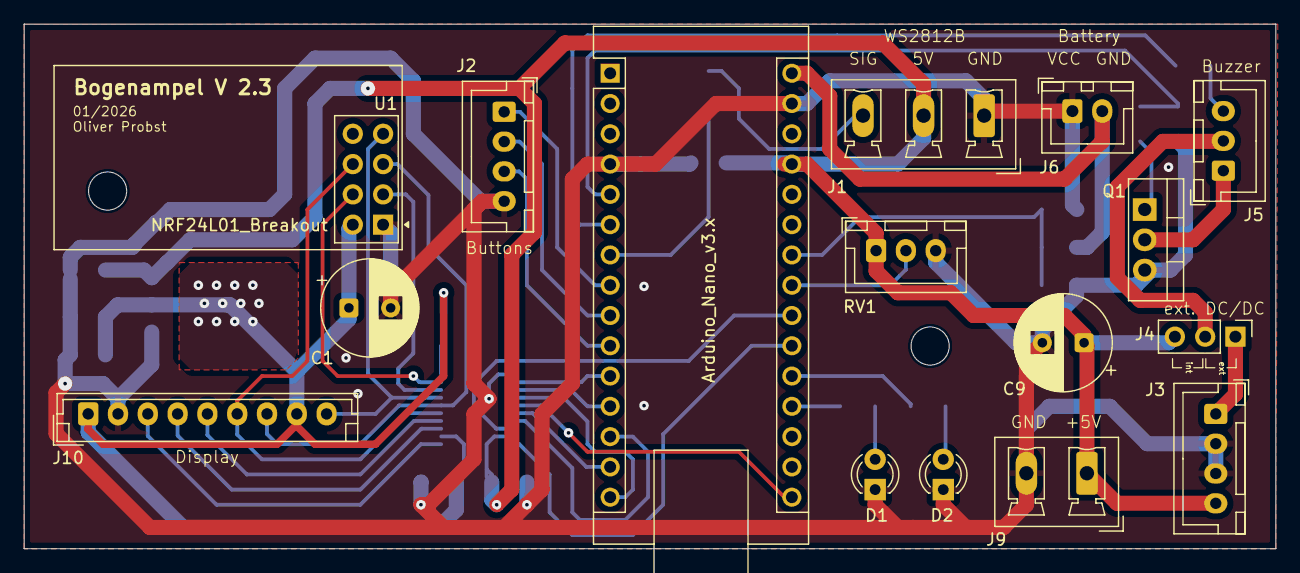
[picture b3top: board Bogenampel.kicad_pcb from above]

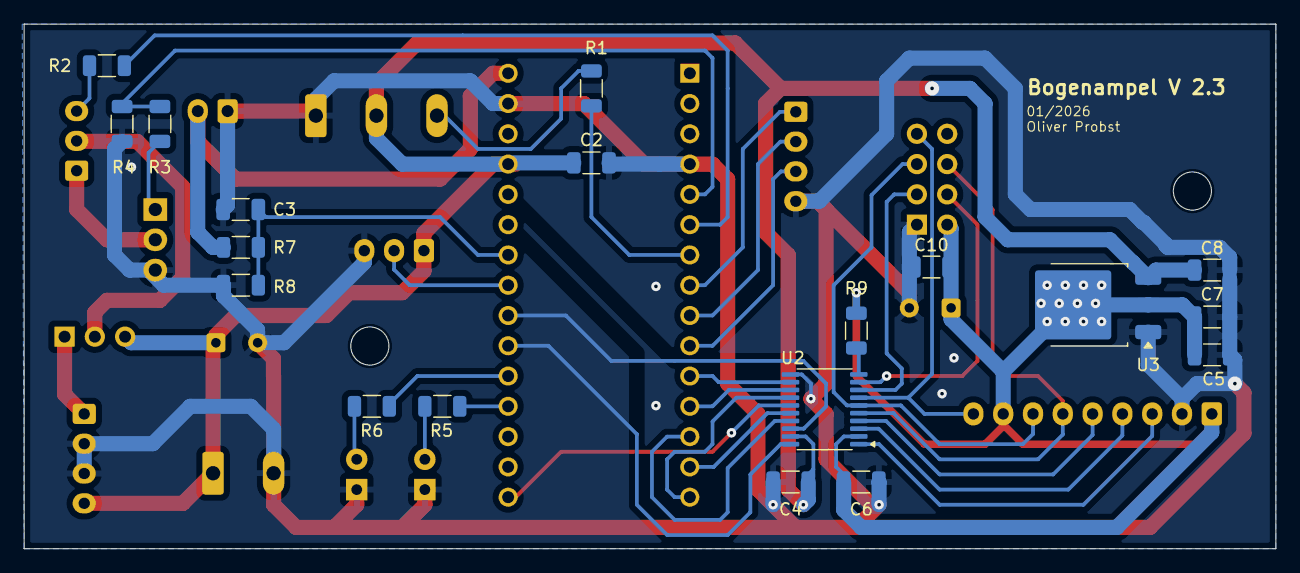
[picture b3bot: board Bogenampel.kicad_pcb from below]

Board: 2 copper layers, 105.0 x 44.0 mm, 35 parts (19 on the bottom side), 39 nets.

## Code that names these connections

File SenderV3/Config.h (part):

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 * Hardware: ESP32-S3-WROOM-1U-N16R8 ("Universal-Fernbedienung", IC2)
 * - Waveshare 1.54" e-Paper V2 (SSD1681, 200x200) als rohes Panel an J1
 * - ESP-NOW Funk (integriert, kein externes Modul)
 * - 2 Taster (SW2/GPIO15 = CONFIG + Einschalten, SW1/GPIO9 = OK), Power-Latch (TPS62742)
 * - LiPo-Lader MCP73837, Batteriespannungsmessung über Teiler
 *
 * Verbindliche Pin-Quelle: specs/004-v3-esp32-port/contracts/hardware-pins.md
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    //-------------------------------------------------------------------------
    // Power-Management (TPS62742 + Latch)
    //-------------------------------------------------------------------------
    constexpr uint8_t LATCH = 16;  // über D1 (BAS40-05) an EN des TPS62742;
                                   // ERSTE Aktion in setup(): OUTPUT + HIGH!
                                   // LOW = Selbstabschaltung
    constexpr uint8_t LOAD  = 7;   // TPS62742 LOAD-Eingang: schaltet 3V3_LOAD-Rail
                                   // fürs Display; HIGH vor Display-Init, LOW vor Power-Off

    //-------------------------------------------------------------------------
    // Taster (SW2 = BTN1, SW1 = BTN2) — die Namen bezeichnen den PIN, nicht die
    // Bedienrolle. Die Rollen sind in ButtonManager::readRawState() zugeordnet
    // und wurden an die Gehäusebeschriftung angepasst:
    //   BTN1 (GPIO15) → Rolle CONFIG (Weiter/Ändern), zugleich Einschalt-Taster
    //   BTN2 (GPIO9)  → Rolle OK (Bestätigen, Alarm 2s, Power-Off 3s)
    // Welcher Taster einschaltet, legt der Power-Latch in der Hardware fest.
    //-------------------------------------------------------------------------
    constexpr uint8_t BTN1 = 15;   // SW2: AKTIV HIGH (externer Teiler
                                   // R2/R7 an +BATT, 100nF C1); KEINE internen Pulls!
    constexpr uint8_t BTN2 = 9;    // SW1: gegen GND, INPUT_PULLUP, aktiv LOW

    //-------------------------------------------------------------------------
    // Batterie / USB / Lader (MCP73837)
    //-------------------------------------------------------------------------
    constexpr uint8_t ADC_BAT = 10;  // ADC1_CH9, Teiler R4/R8 = 150k/100k an +BATT
                                     // → V_BAT = V_ADC × 2,5 (Sensor stromlos wenn aus)
    constexpr uint8_t USB_CON = 8;   // VBUS-Teiler (R16/R18), aktiv HIGH bei USB
    constexpr uint8_t C_ST1   = 11;  // Lader STAT1 (Open-Drain → INPUT_PULLUP)
    constexpr uint8_t C_ST2   = 12;  // Lader STAT2 (Open-Drain → INPUT_PULLUP)
    constexpr uint8_t C_PG    = 17;  // Lader Power Good (Open-Drain → INPUT_PULLUP)
    constexpr uint8_t C_PRG   = 18;  // Ladestrom-Umschaltung über R20 an PROG2;
                                     // bleibt INPUT (hochohmig) = Default-Ladestrom

    //-------------------------------------------------------------------------
    // e-Paper (Waveshare 1.54" V2 / SSD1681, rohes Panel an J1, write-only SPI)
    //-------------------------------------------------------------------------
    constexpr uint8_t EPD_CS   = 21;  // J1 Pin 12 (CS_D)
    constexpr uint8_t EPD_DC   = 47;  // J1 Pin 11
    constexpr uint8_t EPD_RST  = 48;  // J1 Pin 10
    constexpr uint8_t EPD_BUSY = 38;  // J1 Pin 9
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
namespace ConfigValidation {

    // BTN1/SW2 liegt auf ADC2 (GPIO15) → darf nur digital gelesen werden (Funk aktiv!)
    static_assert(Pins::BTN1 == 15, "BTN1 must stay on GPIO15 (digital only, ADC2!)");

    // Taster-Pins unterschiedlich
    static_assert(Pins::BTN1 != Pins::BTN2, "Button pins must be unique");

    // ADC_BAT muss auf ADC1 liegen (GPIO1-10 beim ESP32-S3)
    static_assert(Pins::ADC_BAT <= 10, "ADC_BAT must be on ADC1 (radio blocks ADC2)");

    // Partial-Fenster innerhalb des Panels
    static_assert(Display::COUNTDOWN_X + Display::COUNTDOWN_W <= Display::WIDTH,
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
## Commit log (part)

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2025-12-06 added gitignore
2026-05-29 V3 mit XIAO-ESP32C3 Arbeitsstand
2026-05-29 Universalfernbedienung V3
2026-06-09 Update to V3 with ESP-32
